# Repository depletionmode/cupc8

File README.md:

## CUPC/8

###### Documentation
https://github.com/depletionmode/cupc8/blob/master/doc/CUPC8%20Manual.md

###### Blog
http://depletionmode.com/

### Terminal debugger

Build the debugger from `tools/` with:

```sh
nim c -d:release simtui.nim
```

Then run `kernel/debug.sh`. The guest display is embedded by default; use
`kernel/debug.sh --display:window` for the standalone SDL window. Terminal
graphics and color treatment can be selected explicitly:

```sh
kernel/debug.sh --gfx:half --theme:light
kernel/debug.sh --gfx:auto --theme:dark
```

Inside the debugger, `:display embedded|window`, `:theme auto|dark|light`, and
`:gfx auto|kitty|half` switch these modes without restarting. Pane borders can
be dragged with the mouse to resize the layout. Press `?` for the complete
keymap and command reference.

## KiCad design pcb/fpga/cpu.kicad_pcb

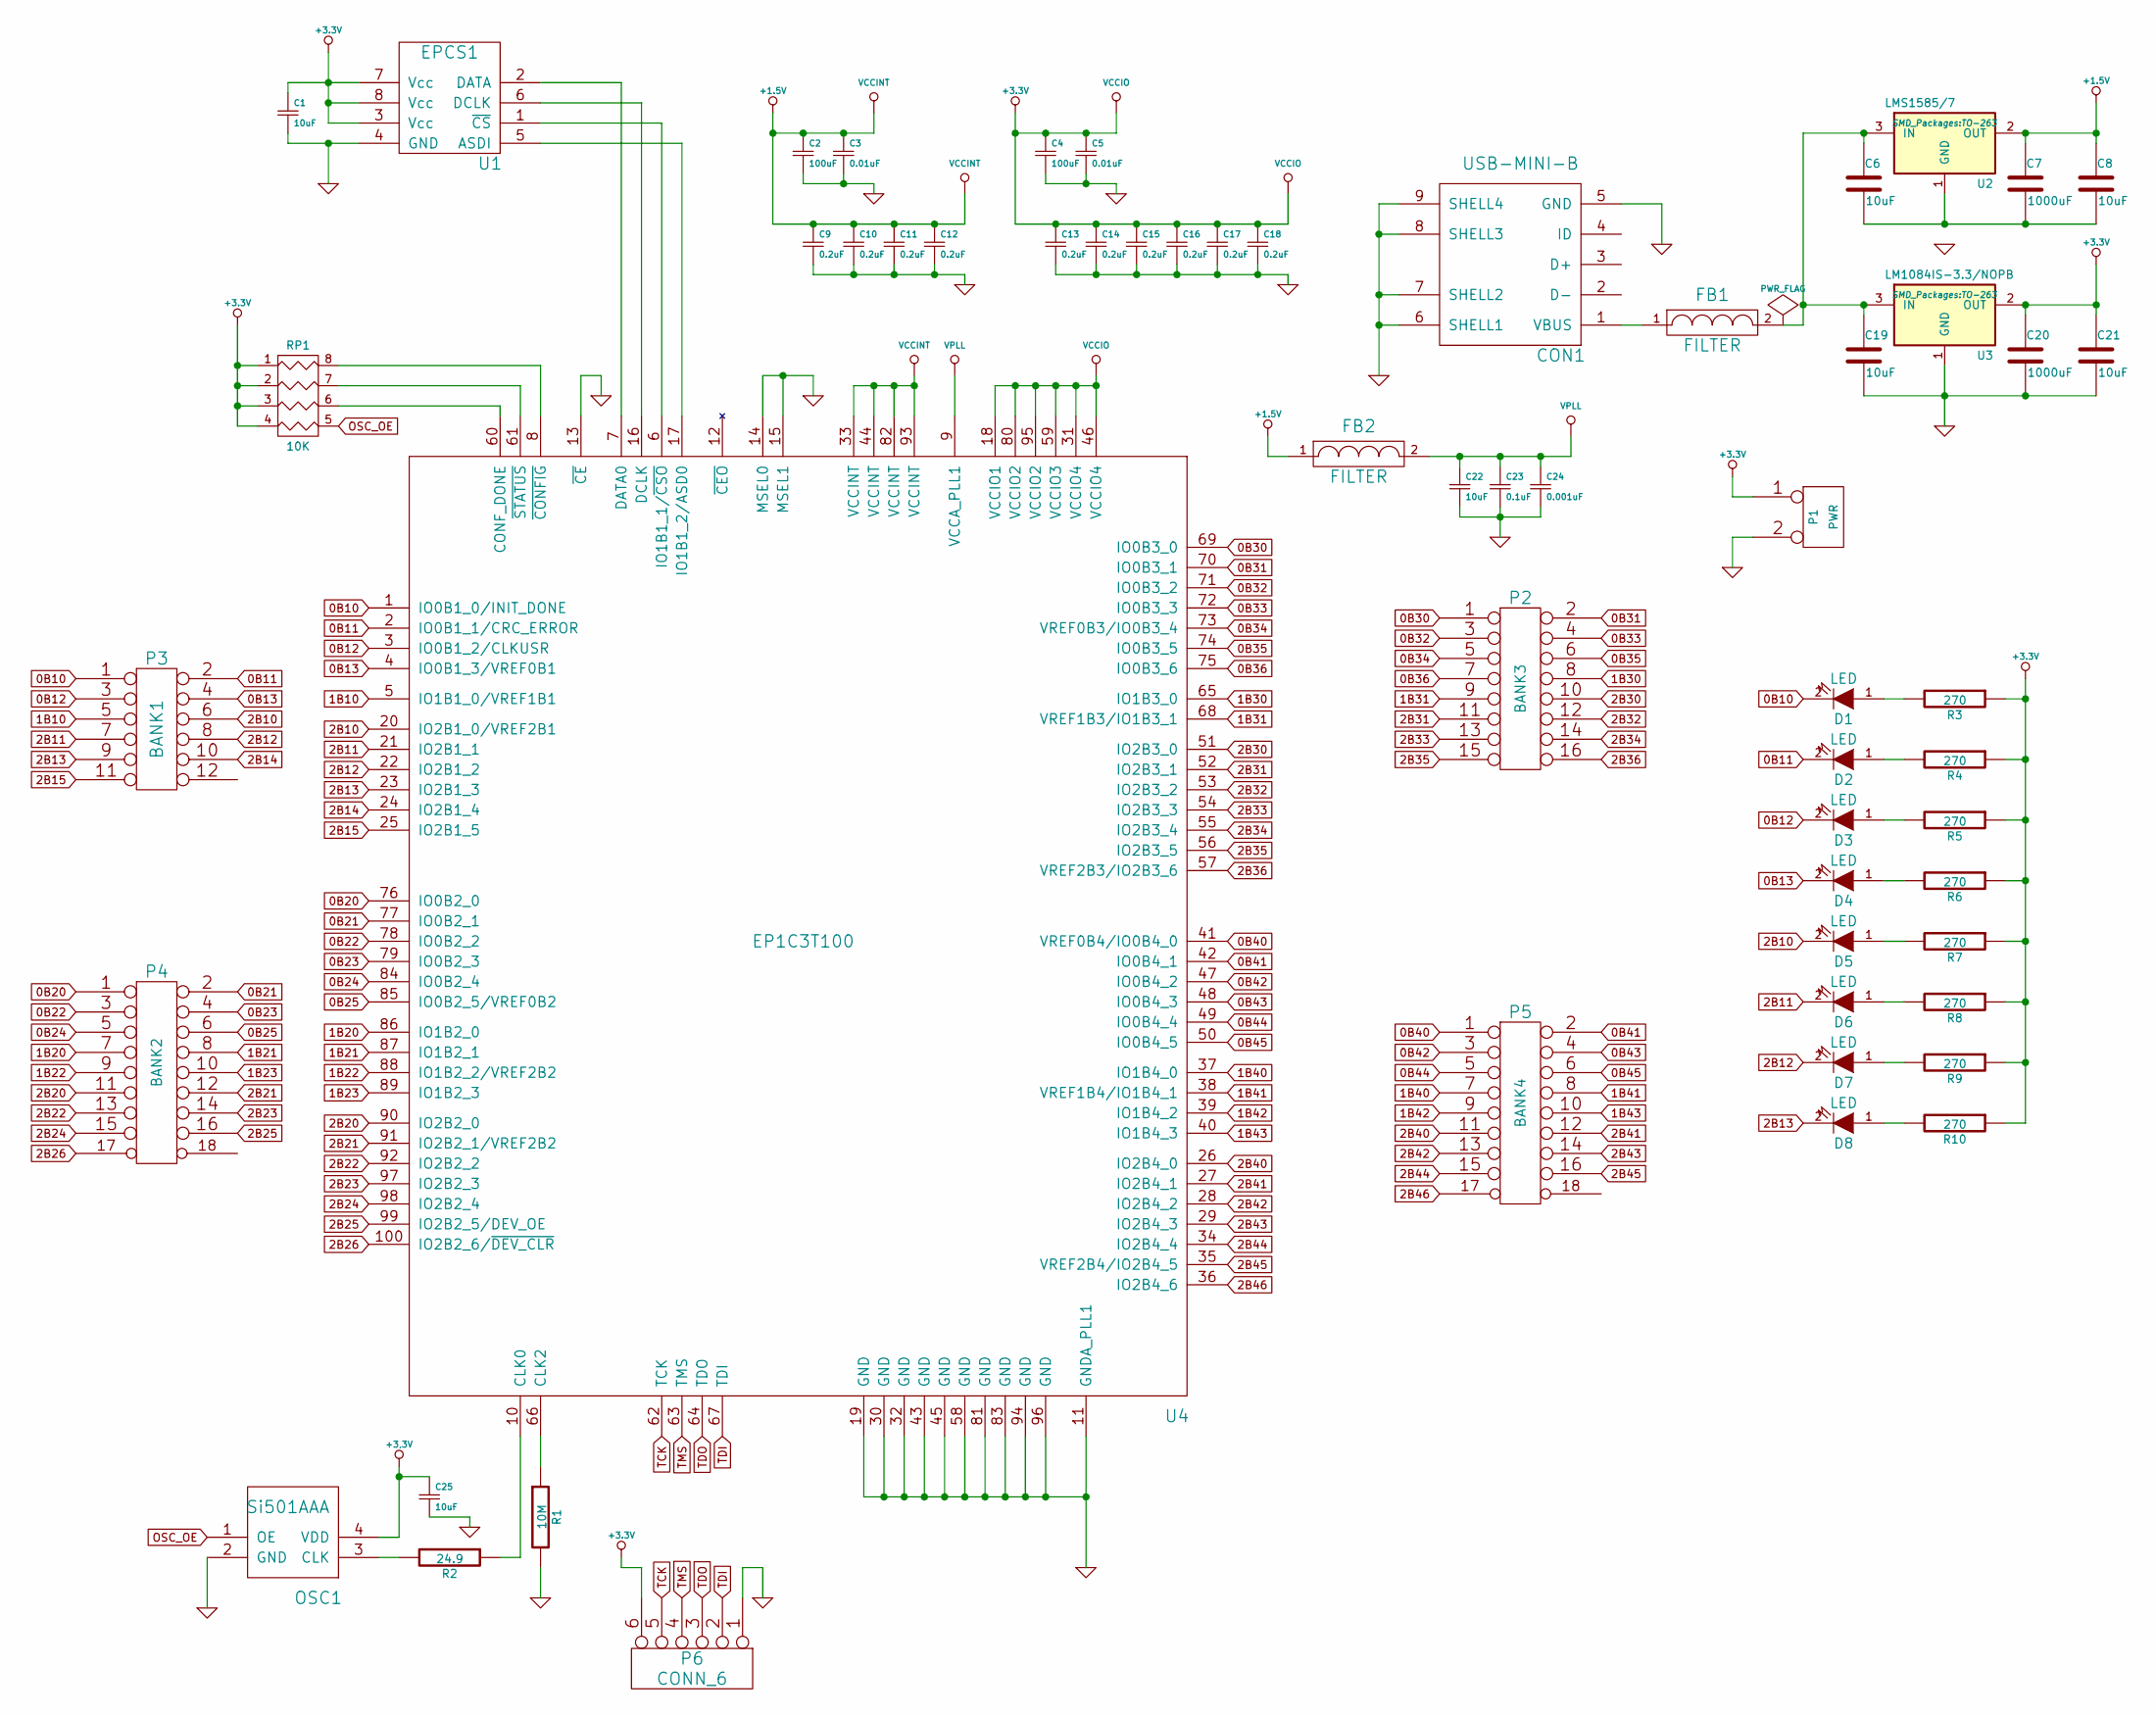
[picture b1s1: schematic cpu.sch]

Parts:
C1: 10uF; C_0805_HandSoldering
C2, C4: 100uF; C_0805_HandSoldering
C3, C5: 0.01uF; C_0805_HandSoldering
C6, C8: 10uF; c_elec_4x4.5
C7: 1000uF; c_elec_4x4.5; PARTNO EEEFK0J102AP
C9, C10, C11, C12, C13, C14, C15, C16, C17, C18: 0.2uF; C_0805_HandSoldering
C19, C21, C22: 10uF; c_elec_4x5.3
C20: 1000uF; c_elec_4x5.3; PARTNO EEEFK0J102AP
C23: 0.1uF; C_0805
C24: 0.001uF; C_0805
C25: 10uF; C_0805
CON1: USB-MINI-B; USB_Mini-B
D1: LED; LED-0805; PARTNO 5988150107F
D2, D3, D4, D5, D6, D7, D8: LED; LED-0805
FB1, FB2: FILTER; R_0805_HandSoldering; PARTNO MMZ2012Y202BT000
OSC1: Si501AAA; DFN4-Si501; PARTNO 501AAA50M0000DAF
P1: PWR; Pin_Header_Straight_1x02
P2: BANK3; Pin_Header_Straight_2x08
P3: BANK1; Pin_Header_Straight_2x06
P4: BANK2; Pin_Header_Straight_2x09
P5: BANK4; Pin_Header_Straight_2x09
P6: CONN_6; Pin_Header_Straight_1x06
R1: 10M; R_0805_HandSoldering
R2: 24.9; R_0805_HandSoldering
R3, R4, R5, R6, R7, R8, R9, R10: 270; R_0805_HandSoldering
RP1: 10K; R_Array_Convex_4x1206; PARTNO YC164-JR-0710KL
U1: EPCS1; SOIC-8-N; PARTNO EPCS1
U2: LMS1585/7; TO-263
U3: LM1084IS-3.3/NOPB; TO-263
U4: EP1C3T100; TQFP-100_14x14mm_Pitch0.5mm; PARTNO EP1C3T100C8N

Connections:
0B10: D1.2 (K), P3.1, U4.1 (IO0B1_0/INIT_DONE)
0B11: D2.2 (K), P3.2, U4.2 (IO0B1_1/CRC_ERROR)
0B12: D3.2 (K), P3.3, U4.3 (IO0B1_2/CLKUSR)
0B13: D4.2 (K), P3.4, U4.4 (IO0B1_3/VREF0B1)
0B20: P4.1, U4.76 (IO0B2_0)
0B21: P4.2, U4.77 (IO0B2_1)
0B22: P4.3, U4.78 (IO0B2_2)
0B23: P4.4, U4.79 (IO0B2_3)
0B24: P4.5, U4.84 (IO0B2_4)
0B25: P4.6, U4.85 (IO0B2_5/VREF0B2)
0B30: P2.1, U4.69 (IO0B3_0)
0B31: P2.2, U4.70 (IO0B3_1)
0B32: P2.3, U4.71 (IO0B3_2)
0B33: P2.4, U4.72 (IO0B3_3)
0B34: P2.5, U4.73 (VREF0B3/IO0B3_4)
0B35: P2.6, U4.74 (IO0B3_5)
0B36: P2.7, U4.75 (IO0B3_6)
0B40: P5.1, U4.41 (VREF0B4/IO0B4_0)
0B41: P5.2, U4.42 (IO0B4_1)
0B42: P5.3, U4.47 (IO0B4_2)
0B43: P5.4, U4.48 (IO0B4_3)
0B44: P5.5, U4.49 (IO0B4_4)
0B45: P5.6, U4.50 (IO0B4_5)
1B10: P3.5, U4.5 (IO1B1_0/VREF1B1)
1B20: P4.7, U4.86 (IO1B2_0)
1B21: P4.8, U4.87 (IO1B2_1)
1B22: P4.9, U4.88 (IO1B2_2/VREF2B2)
1B23: P4.10, U4.89 (IO1B2_3)
1B30: P2.8, U4.65 (IO1B3_0)
1B31: P2.9, U4.68 (VREF1B3/IO1B3_1)
1B40: P5.7, U4.37 (IO1B4_0)
1B41: P5.8, U4.38 (VREF1B4/IO1B4_1)
1B42: P5.9, U4.39 (IO1B4_2)
1B43: P5.10, U4.40 (IO1B4_3)
2B10: D5.2 (K), P3.6, U4.20 (IO2B1_0/VREF2B1)
2B11: D6.2 (K), P3.7, U4.21 (IO2B1_1)
2B12: D7.2 (K), P3.8, U4.22 (IO2B1_2)
2B13: D8.2 (K), P3.9, U4.23 (IO2B1_3)
2B14: P3.10, U4.24 (IO2B1_4)
2B15: P3.11, U4.25 (IO2B1_5)
2B20: P4.11, U4.90 (IO2B2_0)
2B21: P4.12, U4.91 (IO2B2_1/VREF2B2)
2B22: P4.13, U4.92 (IO2B2_2)
2B23: P4.14, U4.97 (IO2B2_3)
2B24: P4.15, U4.98 (IO2B2_4)
2B25: P4.16, U4.99 (IO2B2_5/DEV_OE)
2B26: P4.17, U4.100 (IO2B2_6/~DEV_CLR)
2B30: P2.10, U4.51 (IO2B3_0)
2B31: P2.11, U4.52 (IO2B3_1)
2B32: P2.12, U4.53 (IO2B3_2)
2B33: P2.13, U4.54 (IO2B3_3)
2B34: P2.14, U4.55 (IO2B3_4)
2B35: P2.15, U4.56 (IO2B3_5)
2B36: P2.16, U4.57 (VREF2B3/IO2B3_6)
2B40: P5.11, U4.26 (IO2B4_0)
2B41: P5.12, U4.27 (IO2B4_1)
2B42: P5.13, U4.28 (IO2B4_2)
2B43: P5.14, U4.29 (IO2B4_3)
2B44: P5.15, U4.34 (IO2B4_4)
2B45: P5.16, U4.35 (VREF2B4/IO2B4_5)
2B46: P5.17, U4.36 (IO2B4_6)
GND: C1.2, C2.2, C3.2, C4.2, C5.2, C9.2, C10.2, C11.2, C12.2, C13.2, C14.2, C15.2, C16.2, C17.2, C18.2, C19.2, C20.2, C21.2, C22.2, C23.2, C24.2, C25.2, CON1.5 (GND), CON1.6 (SHELL1), CON1.7 (SHELL2), CON1.8 (SHELL3), CON1.9 (SHELL4), OSC1.2 (GND), P1.2 (PM), P6.1, R1.2, U1.4 (GND), U3.1 (GND), U4.11 (GNDA_PLL1), U4.13 (~CE), U4.14 (MSEL0), U4.15 (MSEL1), U4.19 (GND), U4.30 (GND), U4.32 (GND), U4.43 (GND), U4.45 (GND), U4.58 (GND), U4.81 (GND), U4.83 (GND), U4.94 (GND), U4.96 (GND)
unnamed: C6.2, C7.2, C8.2, U2.1 (GND)
unnamed: C6.1, C19.1, FB1.2, U2.3 (IN), U3.3 (IN)
unnamed: CON1.1 (VBUS), FB1.1
unnamed: D1.1 (A), R3.2
unnamed: D2.1 (A), R4.2
unnamed: D3.1 (A), R5.2
unnamed: D4.1 (A), R6.2
unnamed: D5.1 (A), R7.2
unnamed: D6.1 (A), R8.2
unnamed: D7.1 (A), R9.2
unnamed: D8.1 (A), R10.2
unnamed: OSC1.3 (CLK), R2.2
unnamed: R1.1, U4.66 (CLK2)
unnamed: R2.1, U4.10 (CLK0)
unnamed: RP1.6 (R3), U4.60 (CONF_DONE)
unnamed: RP1.7 (R2), U4.61 (~STATUS)
unnamed: RP1.8 (R1), U4.8 (~CONFIG)
unnamed: U1.1 (~CS), U4.6 (IO1B1_1/~CSO)
unnamed: U1.2 (DATA), U4.7 (DATA0)
unnamed: U1.5 (ASDI), U4.17 (IO1B1_2/ASD0)
unnamed: U1.6 (DCLK), U4.16 (DCLK)
OSC_OE: OSC1.1 (OE), RP1.5 (R4)
TCK: P6.5, U4.62 (TCK)
TDI: P6.2, U4.67 (TDI)
TDO: P6.3, U4.64 (TDO)
TMS: P6.4, U4.63 (TMS)
VCCINT: C2.1, C3.1, C7.1, C8.1, C9.1, C10.1, C11.1, C12.1, FB2.1, U2.2 (OUT), U4.33 (VCCINT), U4.44 (VCCINT), U4.82 (VCCINT), U4.93 (VCCINT)
VPLL: C22.1, C23.1, C24.1, FB2.2, U4.9 (VCCA_PLL1)

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
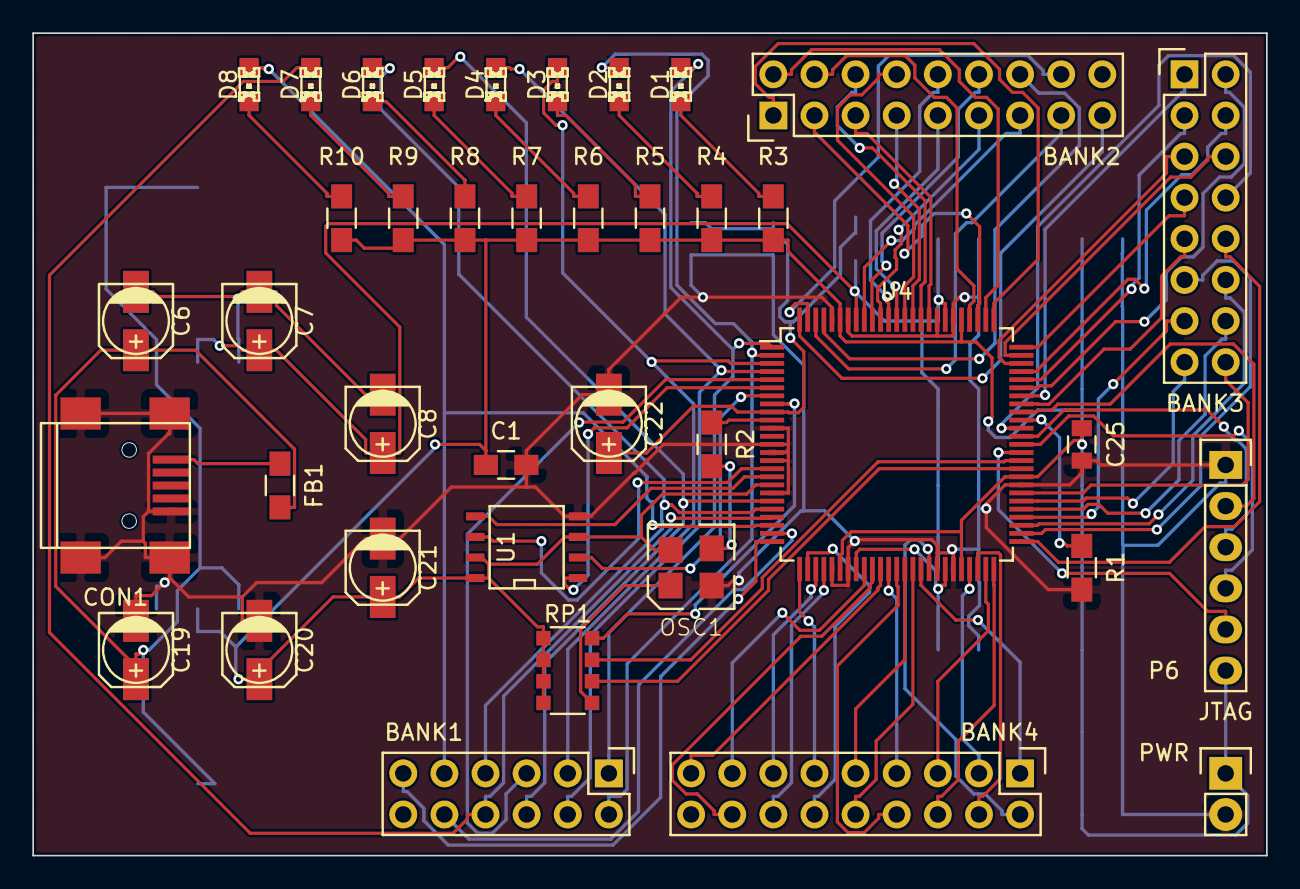
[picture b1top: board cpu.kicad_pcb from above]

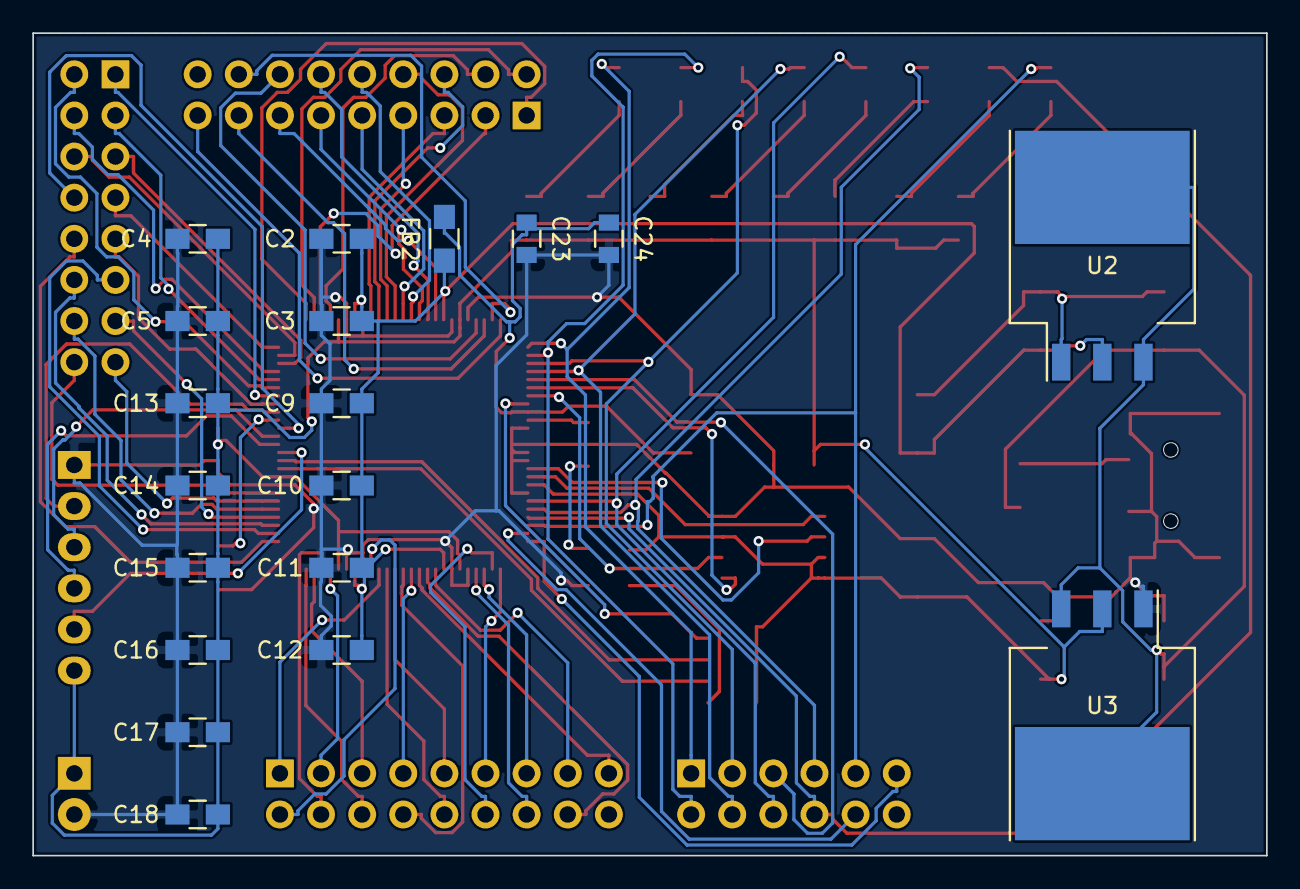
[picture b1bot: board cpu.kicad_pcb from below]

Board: 2 copper layers, 76.2 x 50.8 mm, 58 parts (19 on the bottom side), 91 nets.
